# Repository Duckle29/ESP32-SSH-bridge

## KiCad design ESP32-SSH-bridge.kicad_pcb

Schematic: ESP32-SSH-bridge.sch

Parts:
C1: 10uF; CP_Radial_D6.3mm_P2.50mm
J1, J2: Conn_01x07; PinSocket_1x07_P2.54mm_Vertical
J3: DB9_Female_MountingHoles; DSUB-9_Female_Horizontal_P2.77x2.84mm_EdgePinOffset9.90mm_H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
J4: +5V; PinHeader_1x02_P2.54mm_Horizontal

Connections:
+3V3: C1.1, J2.1
+5V: J1.1, J4.2; also elsewhere on the board
/MRXSTX_HV: J3.3; also elsewhere on the board
/MRXSTX_LV: J2.6; also elsewhere on the board
/MTXSRX_HV: J3.2; also elsewhere on the board
/MTXSRX_LV: J2.7; also elsewhere on the board
GND: C1.2, J1.2, J2.2, J3.0, J3.5, J4.1; also elsewhere on the board

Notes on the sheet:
Dirty ESP32-dev

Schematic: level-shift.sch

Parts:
C2, C3, C4, C5: 1uF; C_0805_2012Metric_Pad1.15x1.40mm_HandSolder
U1: MAX232I; SOIC-16_3.9x9.9mm_P1.27mm

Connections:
+5V: U1.16 (VCC); also elsewhere on the board
/MRXSTX_HV: U1.8 (R2IN); also elsewhere on the board
/MRXSTX_LV: U1.9 (R2OUT); also elsewhere on the board
/MTXSRX_HV: U1.7 (T2OUT); also elsewhere on the board
/MTXSRX_LV: U1.10 (T2IN); also elsewhere on the board
GND: C4.1, C5.1, U1.15 (GND); also elsewhere on the board
unnamed: C2.1, U1.3 (C1-)
unnamed: C2.2, U1.1 (C1+)
unnamed: C3.1, U1.4 (C2+)
unnamed: C3.2, U1.5 (C2-)
unnamed: C4.2, U1.2 (VS+)
unnamed: C5.2, U1.6 (VS-)

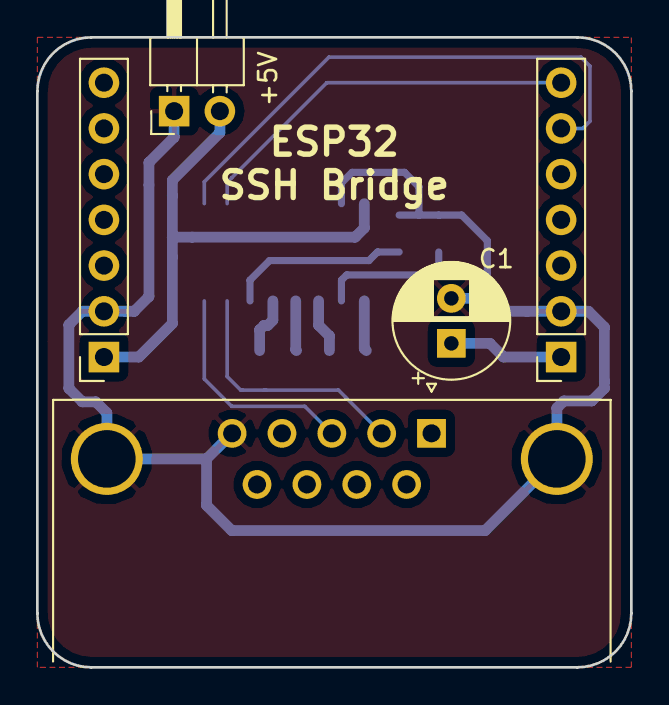
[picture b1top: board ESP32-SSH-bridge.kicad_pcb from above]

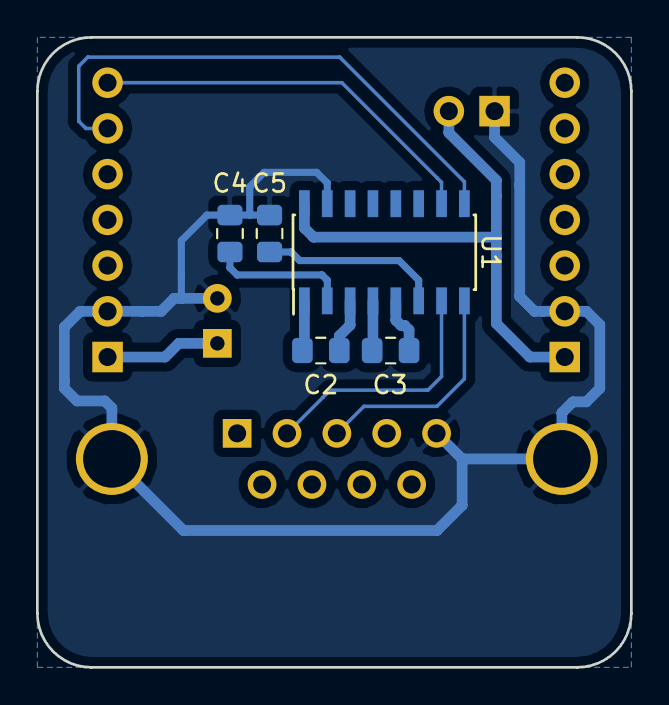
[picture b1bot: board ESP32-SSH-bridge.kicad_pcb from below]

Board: 2 copper layers, 33.0 x 35.0 mm, 10 parts (5 on the bottom side), 13 nets.

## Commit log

2018-09-01 Initial commit of the version that takes a simple plug-in dev board
2018-09-01 added readme
